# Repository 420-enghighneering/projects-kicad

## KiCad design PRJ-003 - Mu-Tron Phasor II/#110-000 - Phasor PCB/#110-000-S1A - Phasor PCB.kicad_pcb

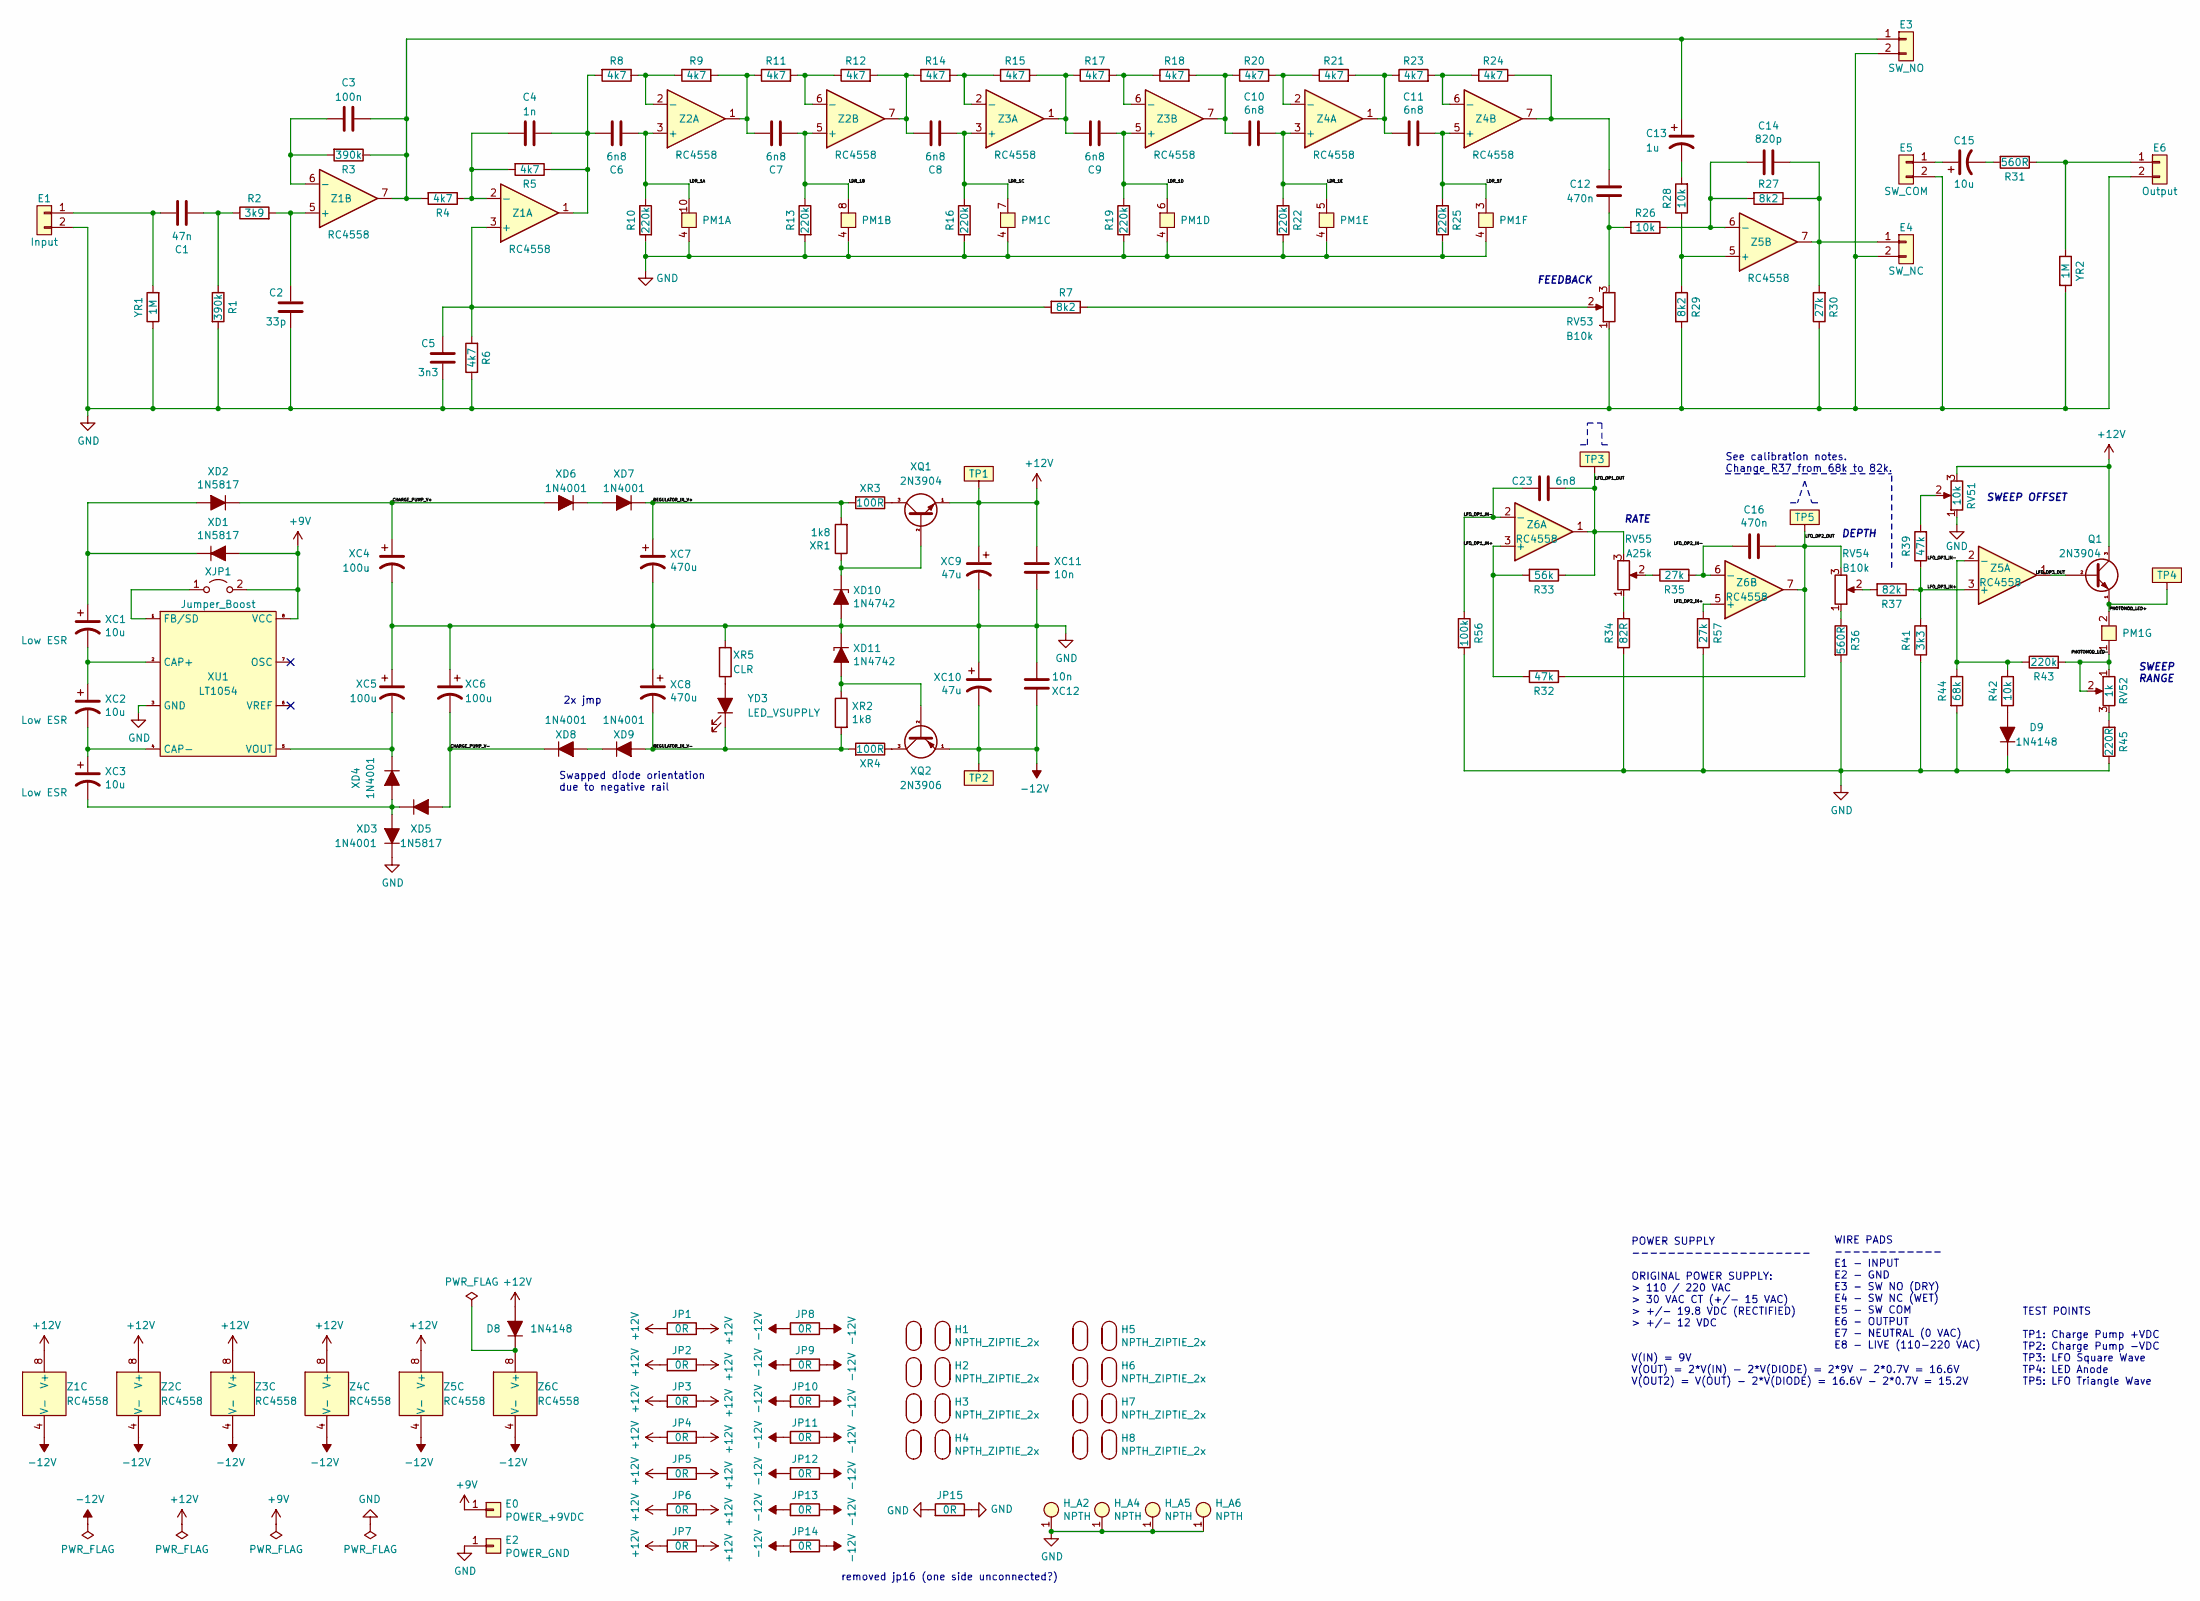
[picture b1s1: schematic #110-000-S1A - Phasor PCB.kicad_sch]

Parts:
C1: 47n; C_MKS2F024701C00KSSD
C2: 33p; C_FKP2O100331D00JSSD
C3: 100n; C_MKS2C031001A00KSSD
C4: 1n; C_FKS2G011001A00KSSD
C5: 3n3; C_FKS2G013301A00KSSD
C6, C7, C8, C9, C10, C11, C23: 6n8; C_FKS2G016801B00KSSD
C12, C16: 470n; C_MKS2C034701C00KSSD
C13: 1u; C_UMA1H010MDD
C14: 820p; C_FKP2J008201D00HSSD
C15: 10u; C_UMA1V100MDD
D8, D9: 1N4148; D_P10.16_DO35
E0: POWER_+9VDC; E_WIRE_PAD_1x_ZIPTIE_NPTH_2x
E1: Input; E_WIRE_PAD_1x_SHIELD_PAD_1x_ZIPTIE_NPTH_2x
E2: POWER_GND; E_WIRE_PAD_1x_ZIPTIE_NPTH_2x
E3: SW_NO; E_WIRE_PAD_1x_SHIELD_PAD_1x_ZIPTIE_NPTH_2x
E4: SW_NC; E_WIRE_PAD_1x_SHIELD_PAD_1x_ZIPTIE_NPTH_2x
E5: SW_COM; E_WIRE_PAD_1x_SHIELD_PAD_1x_ZIPTIE_NPTH_2x
E6: Output; E_WIRE_PAD_1x_SHIELD_PAD_1x_ZIPTIE_NPTH_2x
H1, H2, H3, H4, H5, H6, H7, H8: NPTH_ZIPTIE_2x; E_ZIPTIE_NPTH_2x_P2.54mm
H_A2, H_A4, H_A5, H_A6: NPTH; E_MH_PAD_M3_VIA_HEXSPACER
JP1, JP2, JP3, JP4, JP5, JP6, JP7, JP8, JP9, JP10, JP11, JP12, JP13, JP14, JP15: 0R; R_0R_JUMPER_P10.16
PM1: Photomodule; PM_DIP-10
Q1: 2N3904; Q_P2.54
R1, R3: 390k; R_CF_P10.16_390k
R2: 3k9; R_CF_P10.16_3k9
R4, R5, R6, R8, R9, R11, R12, R14, R15, R17, R18, R20, R21, R23, R24: 4k7; R_CF_P10.16_4k7
R7, R27, R29: 8k2; R_CF_P10.16_8k2
R10, R13, R16, R19, R22, R25, R43: 220k; R_CF_P10.16_220k
R26, R28, R42: 10k; R_CF_P10.16_10k
R30, R35, R57: 27k; R_CF_P10.16_27k
R31, R36: 560R; R_CF_P10.16_560R
R32, R39: 47k; R_CF_P10.16_47k
R33: 56k; R_CF_P10.16_56k
R34: 82R; R_CF_P10.16_82R
R37: 82k; R_CF_P10.16_82k
R41: 3k3; R_CF_P10.16_3k3
R44: 68k; R_CF_P10.16_68k
R45: 220R; R_CF_P10.16_220R
R56: 100k; R_CF_P10.16_100k
RV51: 10k; R_TRIM
RV52: 1k; R_TRIM
RV53, RV54: B10k; R_POT
RV55: A25k; R_POT
TP1: TP1; TP_SMD_R_3mm
TP2: TP2; TP_SMD_R_3mm
TP3: TP3; TP_SMD_R_3mm
TP4, TP5: TP5; TP_SMD_R_3mm
XC1, XC2, XC3: 10u; C_UMA1V100MDD
XC4, XC5, XC6: 100u; C_UMA1E101MDD
XC7, XC8: 470u; C_ANGLED
XC9, XC10: 47u; C_UMA1V470MDD
XC11, XC12: 10n; C_FKS2G021001C00KSSD
XD1, XD2, XD5: 1N5817; D_P10.16_5817
XD3, XD4, XD6, XD7, XD8, XD9: 1N4001; D_P10.16_4001
XD10, XD11: 1N4742; D_P10.16_DO35
XJP1: Jumper_Boost; R_0603_1608M
XQ1: 2N3904; Q_P2.54
XQ2: 2N3906; Q_P2.54
XR1, XR2: 1k8; R_CF_P10.16_1k8
XR3, XR4: 100R; R_CF_P10.16_100R
XR5: CLR; R_CF_P10.16_2k2
XU1: LT1054; U_DIP-8_LT1054_SOCKETED
YD3: LED_VSUPPLY; E_WIRE_PAD_2x_ZIPTIE_NPTH_2x_CIRC
YR1, YR2: 1M; R_CF_P10.16_1M
Z1, Z2, Z3, Z4, Z5, Z6: RC4558; U_DIP-8

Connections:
+9V: E0.1, XD1.1 (A), XJP1.2 (B), XU1.8 (VCC)
+12V: D8.1 (A), JP1.1, JP1.2, JP2.1, JP2.2, JP3.1, JP3.2, JP4.1, JP4.2, JP5.1, JP5.2, JP6.1, JP6.2, JP7.1, JP7.2, Q1.3 (C), RV51.3, TP1.1, XC9.1, XC11.1, XQ1.1 (E), Z1.8 (V+), Z2.8 (V+), Z3.8 (V+), Z4.8 (V+), Z5.8 (V+)
-12V: JP8.1, JP8.2, JP9.1, JP9.2, JP10.1, JP10.2, JP11.1, JP11.2, JP12.1, JP12.2, JP13.1, JP13.2, JP14.1, JP14.2, TP2.1, XC10.2, XC12.1, XQ2.1 (E), Z1.4 (V-), Z2.4 (V-), Z3.4 (V-), Z4.4 (V-), Z5.4 (V-), Z6.4 (V-)
/CHARGE_PUMP_V+: XC4.1, XD2.2 (K), XD6.1 (A)
/CHARGE_PUMP_V-: XC6.2, XD5.1 (A), XD8.2 (K)
/LDR_1A: C6.2, PM1.10, R10.1, Z2.3 (+)
/LDR_1B: C7.2, PM1.8, R13.1, Z2.5 (+)
/LDR_1C: C8.2, PM1.7, R16.1, Z3.3 (+)
/LDR_1D: C9.2, PM1.6, R19.1, Z3.5 (+)
/LDR_1E: C10.1, PM1.5, R22.2, Z4.3 (+)
/LDR_1F: C11.1, PM1.3, R25.2, Z4.5 (+)
/LFO_OP1_IN+: R32.1, R33.2, Z6.3 (+)
/LFO_OP1_IN-: C23.1, R56.1, Z6.2 (-)
/LFO_OP1_OUT: C23.2, R33.1, RV55.3, TP3.1, Z6.1
/LFO_OP2_IN+: R57.1, Z6.5 (+)
/LFO_OP2_IN-: C16.1, R35.2, Z6.6 (-)
/LFO_OP2_OUT: C16.2, R32.2, RV54.3, TP5.1, Z6.7
/LFO_OP3_OUT: Q1.2 (B), Z5.1
/PHOTOMOD_LED+: PM1.2, Q1.1 (E), TP4.1
/PHOTOMOD_LED-: PM1.1, R43.2, RV52.1, RV52.2
/REGULATOR_IN_V+: XC7.1, XD7.2 (K), XR1.2, XR3.2
/REGULATOR_IN_V-: XC8.2, XD9.1 (A), XR2.2, XR4.2, YD3.1 (K)
GND: C2.2, C5.2, D9.2 (K), E1.2, E2.1, E3.2, E4.2, E5.2, E6.2, H_A2.1, H_A4.1, H_A5.1, H_A6.1, JP15.1, JP15.2, PM1.4, PM1.9, R1.2, R6.1, R10.2, R13.2, R16.2, R19.2, R22.1, R25.1, R29.2, R30.1, R34.2, R36.2, R41.1, R44.2, R45.1, R56.2, R57.2, RV51.1, RV53.1, XC4.2, XC5.1, XC6.1, XC7.2, XC8.1, XC9.2, XC10.1, XC11.2, XC12.2, XD3.2 (K), XD10.1 (A), XD11.2 (K), XR5.2, XU1.3 (GND), YR1.1, YR2.2
unnamed: C1.1, R1.1, R2.1
unnamed: C1.2, E1.1, YR1.2
unnamed: C2.1, R2.2, Z1.5 (+)
unnamed: C3.2, R3.2, Z1.6 (-)
unnamed: C4.1, C6.1, R5.1, R8.2, Z1.1
unnamed: C4.2, R4.1, R5.2, Z1.2 (-)
unnamed: C5.1, R6.2, R7.2, Z1.3 (+)
unnamed: C7.1, R9.2, R11.1, Z2.1
unnamed: C8.1, R12.2, R14.1, Z2.7
unnamed: C9.1, R15.2, R17.1, Z3.1
unnamed: C10.2, R18.2, R20.1, Z3.7
unnamed: C11.2, R21.2, R23.1, Z4.1
unnamed: C12.1, R24.1, Z4.7
unnamed: C12.2, R26.2, RV53.3
unnamed: C3.1, C13.1, E3.1, R3.1, R4.2, Z1.7
unnamed: C13.2, R28.2
unnamed: C14.1, R26.1, R27.2, Z5.6 (-)
unnamed: C14.2, E4.1, R27.1, R30.2, Z5.7
unnamed: C15.1, E5.1
unnamed: C15.2, R31.2
unnamed: D8.2 (K), Z6.8 (V+)
unnamed: D9.1 (A), R42.2
unnamed: E6.1, R31.1, YR2.1
unnamed: R7.1, RV53.2
unnamed: R8.1, R9.1, Z2.2 (-)
unnamed: R11.2, R12.1, Z2.6 (-)
unnamed: R14.2, R15.1, Z3.2 (-)
unnamed: R17.2, R18.1, Z3.6 (-)
unnamed: R20.2, R21.1, Z4.2 (-)
unnamed: R23.2, R24.2, Z4.6 (-)
unnamed: R28.1, R29.1, Z5.5 (+)
unnamed: R34.1, RV55.1
unnamed: R35.1, RV55.2
unnamed: R36.1, RV54.1
unnamed: R37.2, RV54.2
unnamed: R39.2, RV51.2
unnamed: R45.2, RV52.3
unnamed: XC1.1, XD1.2 (K), XD2.1 (A)
unnamed: XC1.2, XC2.1, XU1.2 (CAP+)
unnamed: XC2.2, XC3.1, XU1.4 (CAP-)
unnamed: XC3.2, XD3.1 (A), XD4.1 (A), XD5.2 (K)
unnamed: XC5.2, XD4.2 (K), XU1.5 (VOUT)
unnamed: XD6.2 (K), XD7.1 (A)
unnamed: XD8.1 (A), XD9.2 (K)
unnamed: XD10.2 (K), XQ1.2 (B), XR1.1
unnamed: XD11.1 (A), XQ2.2 (B), XR2.1
unnamed: XJP1.1 (A), XU1.1 (FB/SD)
unnamed: XQ1.3 (C), XR3.1
unnamed: XQ2.3 (C), XR4.1
unnamed: XR5.1, YD3.2 (A)

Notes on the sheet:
Swapped diode orientation due to negative rail
2x jmp
removed jp16 (one side unconnected?)
FEEDBACK
RATE
POWER SUPPLY -------------------- ORIGINAL POWER SUPPLY: > 110 / 220 VAC > 30 VAC CT (+/- 15 VAC) > +/- 19.8 VDC (RECTIFIED) > +/- 12 VDC V(IN) = 9V V(OUT) = 2*V(IN) - 2*V(DIODE) = 2*9V - 2*0.7V = 16.6V V(OUT2) = V(OUT) - 2*V(DIODE) = 16.6V - 2*0.7V = 15.2V
See calibration notes. Change R37 from 68k to 82k.
WIRE PADS ------------ E1 - INPUT E2 - GND E3 - SW NO (DRY) E4 - SW NC (WET) E5 - SW COM E6 - OUTPUT E7 - NEUTRAL (0 VAC) E8 - LIVE (110-220 VAC)
DEPTH
SWEEP OFFSET
TEST POINTS TP1: Charge Pump +VDC TP2: Charge Pump -VDC TP3: LFO Square Wave TP4: LED Anode TP5: LFO Triangle Wave
SWEEP RANGE

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
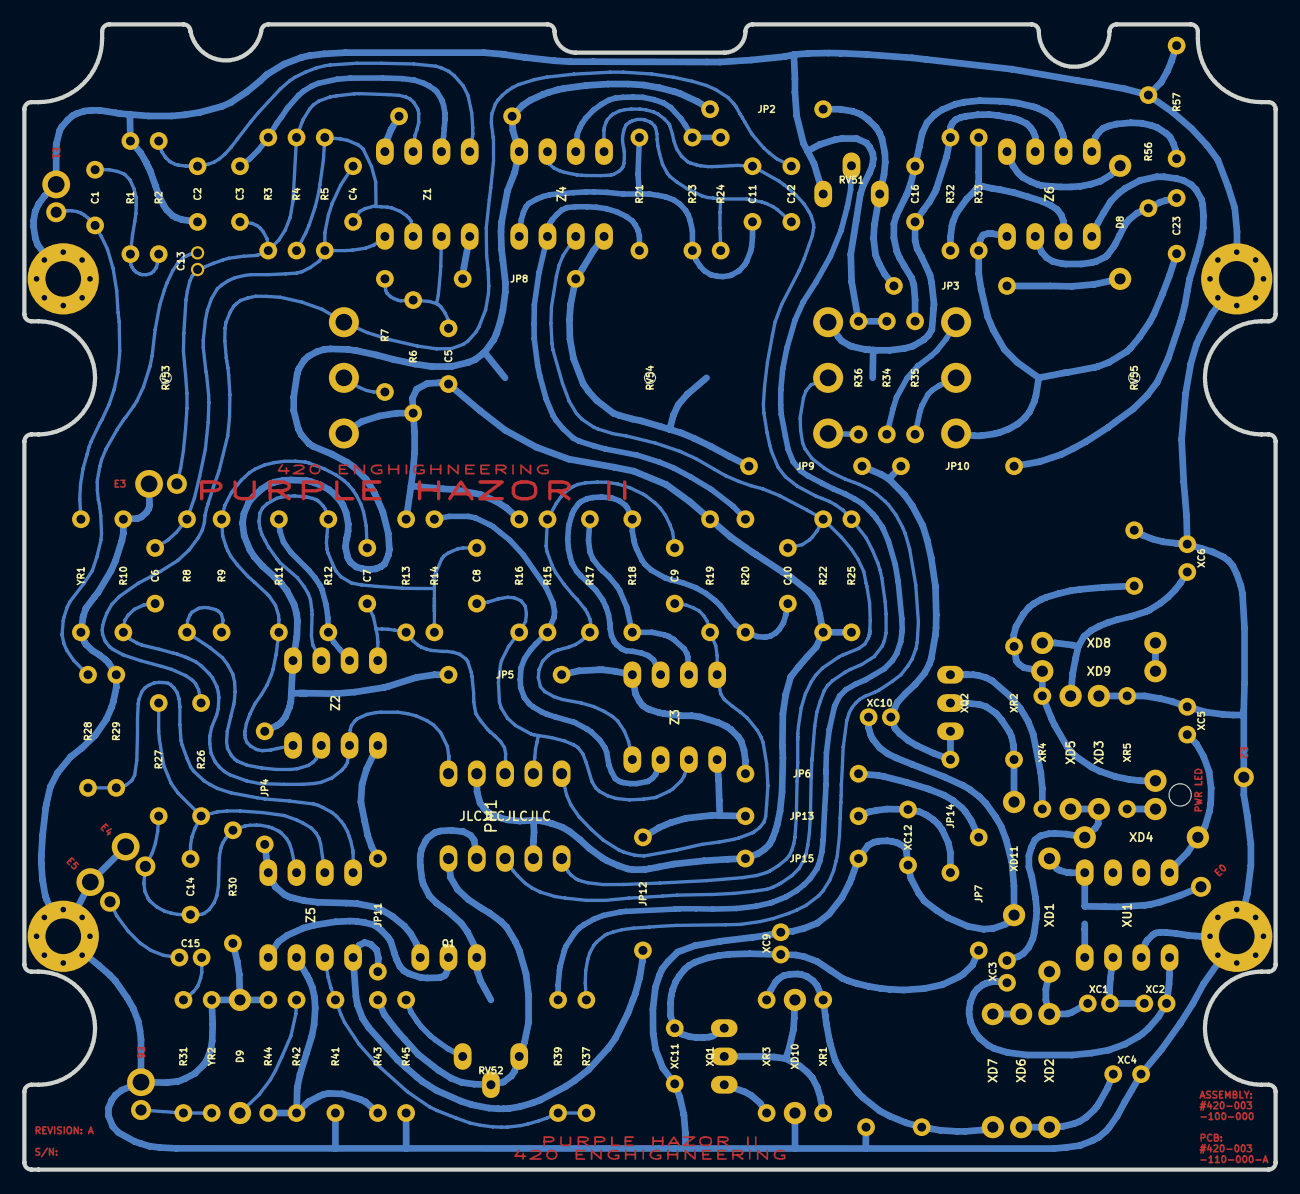
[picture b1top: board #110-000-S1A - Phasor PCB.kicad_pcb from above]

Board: 2 copper layers, 112.4 x 102.9 mm, 151 parts (1 on the bottom side), 75 nets.

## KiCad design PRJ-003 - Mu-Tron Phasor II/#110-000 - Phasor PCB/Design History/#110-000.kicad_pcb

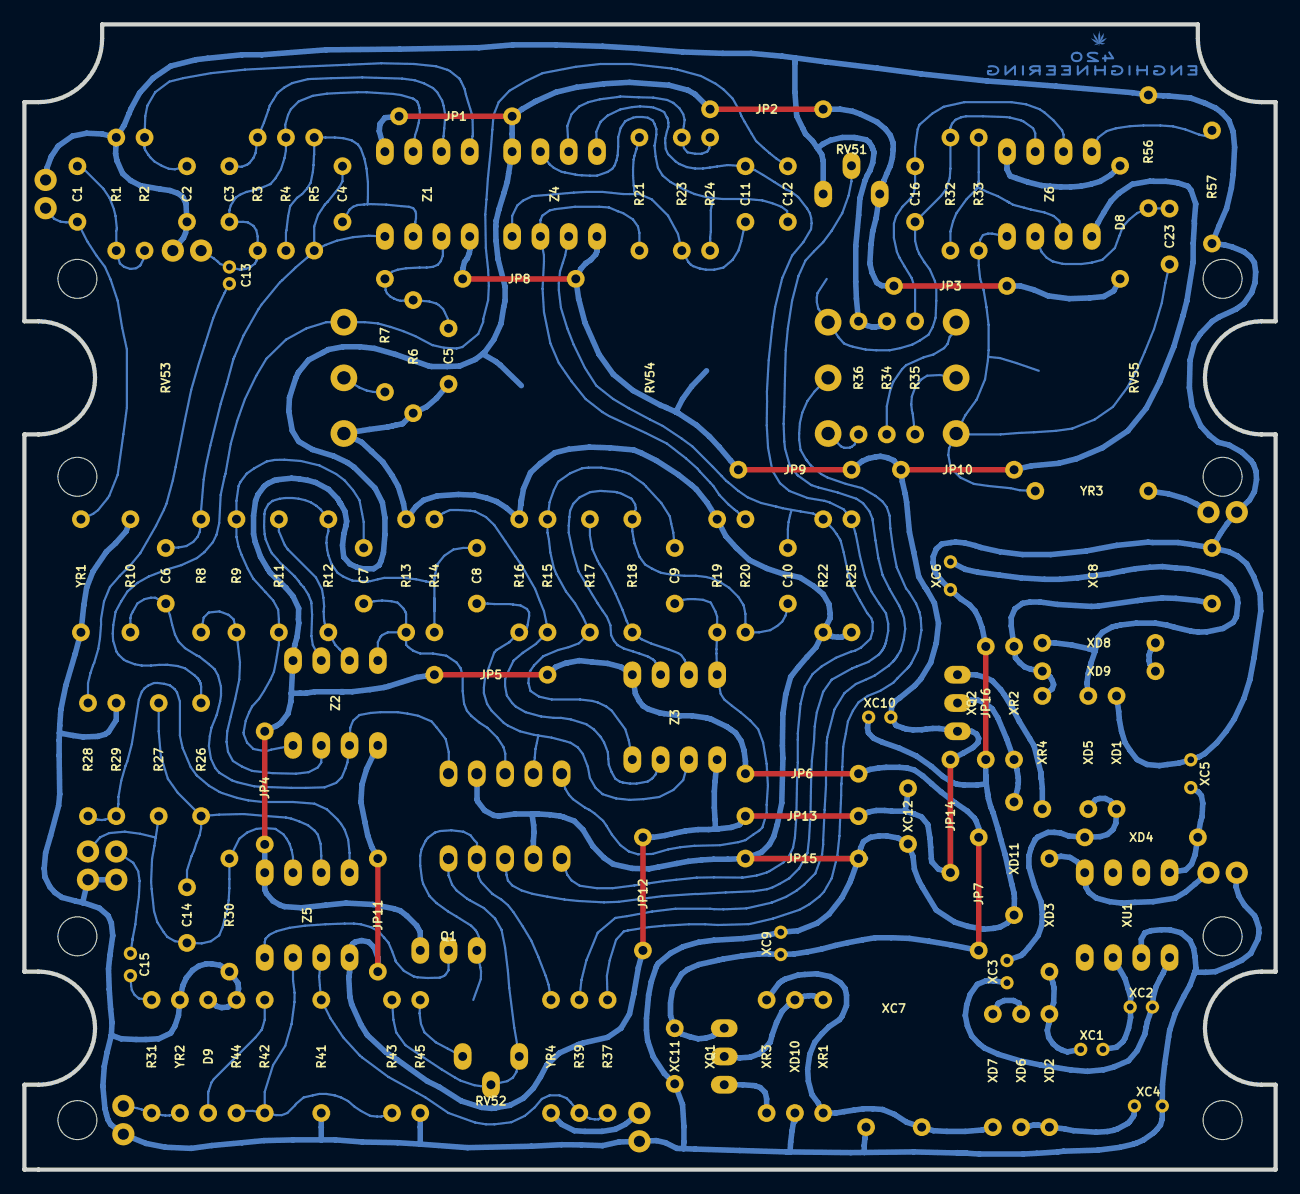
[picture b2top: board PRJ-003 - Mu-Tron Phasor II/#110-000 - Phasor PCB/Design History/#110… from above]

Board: 2 copper layers, 112.4 x 102.9 mm, 155 parts (0 on the bottom side), 75 nets.

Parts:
C1: 47n; C_MKS2F024701C00KSSD
C2: 33p; C_FKP2O100331D00JSSD
C3: 100n; C_MKS2C031001A00KSSD
C4: 1n; C_FKS2G011001A00KSSD
C5: 3n3; C_FKS2G013301A00KSSD
C6, C7, C8, C9, C10, C11, C23: 6n8; C_FKS2G016801B00KSSD
C12, C16: 470n; C_MKS2C034701C00KSSD
C13: 1u; C_UMA1H010MDD
C14: 820p; C_FKP2J008201D00HSSD
C15: 10u; C_UMA1V100MDD
D8, D9: 1N4148; D_P10.16_DO35
E0: Power Supply; E_WIRE_PAD_2x
E1: Input & Shield; E_WIRE_PAD_2x
E3: SW_NO; E_WIRE_PAD_2x
E4: SW_NC; E_WIRE_PAD_2x
E5: SW_COM; E_WIRE_PAD_2x
E6: Output & Shield; E_WIRE_PAD_2x
G1: Logo; Logo_36kdpi
H_A1, H_A2, H_A3, H_A4, H_A5, H_A6, H_A7, H_A8: NPTH; H_NPTH
H_B1, H_B2, H_B3, H_B4, H_B5, H_B6: NPTH; E_ZIPTIE_NPTH
JP1, JP2, JP3, JP4, JP5, JP6, JP7, JP8, JP9, JP10, JP11, JP12, JP13, JP14, JP15, JP16: 0R; R_0R_JUMPER_P10.16
PM1: Photomodule; PM_DIP-10
Q1: 2N3904; Q_P2.54
R1, R3: 390k; R_P10.16
R2: 3k9; R_P10.16
R4, R5, R6, R8, R9, R11, R12, R14, R15, R17, R18, R20, R21, R23, R24: 4k7; R_P10.16
R7, R27, R29: 8k2; R_P10.16
R10, R13, R16, R19, R22, R25, R43: 220k; R_P10.16
R26, R28, R42: 10k; R_P10.16
R30, R35, R57: 27k; R_P10.16
R31, R36: 560R; R_P10.16
R32, R39: 47k; R_P10.16
R33: 56k; R_P10.16
R34: 82R; R_P10.16
R37: 82k; R_P10.16
R41: 3k3; R_P10.16
R44: 68k; R_P10.16
R45: 220R; R_P10.16
R56: 100k; R_P10.16
RV51: 10k; R_TRIM
RV52: 1k; R_TRIM
RV53, RV54: B10k; R_POT
RV55: A25k; R_POT
TP1: TP1; TP_SMD_R_3mm
TP2: TP2; TP_SMD_R_3mm
TP3: TP3; TP_SMD_R_3mm
TP4: TP4; TP_SMD_R_3mm
TP5: TP5; TP_SMD_R_3mm
XC1, XC2, XC3: 10u; C_UMA1V100MDD
XC4, XC5, XC6: 100u; C_UMA1E101MDD
XC7, XC8: 470u; C_ANGLED
XC9, XC10: 47u; C_UMA1V470MDD
XC11, XC12: 10n; C_FKS2G021001C00KSSD
XD1, XD4, XD5, XD6, XD7, XD8, XD9: 1N4001; D_P10.16
XD2, XD3: 1N5817; D_P10.16
XD10, XD11: 1N4742; D_P10.16_DO35
XQ1: 2N3904; Q_P2.54
XQ2: 2N3906; Q_P2.54
XR1, XR2: 1k8; R_P10.16
XR3, XR4: 100R; R_P10.16
XU1: LT1054; U_DIP-8
YD1: LED_RATE_1; E_WIRE_PAD_2x
YD2: LED_RATE_2; E_WIRE_PAD_2x
YR1, YR2: 1M; R_P10.16
YR3, YR4: CLR; R_P10.16
Z1, Z2, Z3, Z4, Z5, Z6: 4558; U_DIP-8

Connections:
+9V: E0.1, XD3.1, XU1.8
+12V: D8.1, JP1.1, JP1.2, JP2.1, JP2.2, JP3.1, JP3.2, JP4.1, JP4.2, JP5.1, JP5.2, JP6.1, JP6.2, JP7.1, JP7.2, Q1.3, RV51.3, TP1.1, XC9.1, XC11.1, XQ1.1, Z1.8, Z2.8, Z3.8, Z4.8, Z5.8
-12V: JP8.1, JP8.2, JP9.1, JP9.2, JP10.1, JP10.2, JP11.1, JP11.2, JP12.1, JP12.2, JP13.1, JP13.2, JP14.1, JP14.2, TP2.1, XC10.2, XC12.2, XQ2.1, Z1.4, Z2.4, Z3.4, Z4.4, Z5.4, Z6.4
GND: C2.2, C5.2, D9.2, E0.2, E1.2, E3.2, E4.2, E5.2, E6.2, JP15.1, JP15.2, JP16.1, JP16.2, PM1.4, PM1.9, R1.1, R6.2, R10.2, R13.2, R16.2, R19.2, R22.2, R25.2, R29.1, R30.1, R34.1, R36.1, R41.2, R44.1, R45.2, R56.1, R57.1, RV51.1, RV53.1, XC4.2, XC5.1, XC6.1, XC7.2, XC8.1, XC9.2, XC10.1, XC11.2, XC12.1, XD1.2, XD10.1, XD11.2, XU1.3, YD1.1, YD2.1, YR1.1, YR2.1
unnamed: C1.1, E1.1, YR1.2
unnamed: C1.2, R1.2, R2.1
unnamed: C2.1, R2.2, Z1.5
unnamed: C3.1, R3.1, Z1.6
unnamed: C4.1, R4.2, R5.1, Z1.2
unnamed: C4.2, C6.1, R5.2, R8.2, Z1.1
unnamed: C5.1, R6.1, R7.2, Z1.3
unnamed: C6.2, PM1.10, R10.1, Z2.3
unnamed: C7.1, R9.1, R11.2, Z2.1
unnamed: C7.2, PM1.8, R13.1, Z2.5
unnamed: C8.1, R12.1, R14.2, Z2.7
unnamed: C8.2, PM1.7, R16.1, Z3.3
unnamed: C9.1, R15.1, R17.2, Z3.1
unnamed: C9.2, PM1.6, R19.1, Z3.5
unnamed: C10.1, R18.1, R20.2, Z3.7
unnamed: C10.2, PM1.5, R22.1, Z4.3
unnamed: C11.1, R21.1, R23.2, Z4.1
unnamed: C11.2, PM1.3, R25.1, Z4.5
unnamed: C12.1, R24.1, Z4.7
unnamed: C12.2, R26.2, RV53.3
unnamed: C3.2, C13.1, E3.1, R3.2, R4.1, Z1.7
unnamed: C13.2, R28.2
unnamed: C14.1, R26.1, R27.2, Z5.6
unnamed: C14.2, E4.1, R27.1, R30.2, Z5.7
unnamed: C15.1, E5.1
unnamed: C15.2, R31.1
unnamed: C16.1, R35.1, Z6.6
unnamed: C16.2, R32.1, RV54.3, TP5.1, Z6.7
unnamed: C23.1, R56.2, Z6.2
unnamed: C23.2, R33.1, RV55.3, TP3.1, YR3.2, Z6.1
unnamed: D8.2, Z6.8
unnamed: D9.1, R42.1
unnamed: E6.1, R31.2, YR2.2
unnamed: PM1.1, R43.1, RV52.1, RV52.2
unnamed: PM1.2, Q1.1, TP4.1, YR4.2
unnamed: Q1.2, Z5.1
unnamed: R7.1, RV53.2
unnamed: R8.1, R9.2, Z2.2
unnamed: R11.1, R12.2, Z2.6
unnamed: R14.1, R15.2, Z3.2
unnamed: R17.1, R18.2, Z3.6
unnamed: R20.1, R21.2, Z4.2
unnamed: R23.1, R24.2, Z4.6
unnamed: R28.1, R29.2, Z5.5
unnamed: R32.2, R33.2, Z6.3
unnamed: R34.2, RV55.1
unnamed: R35.2, RV55.2
unnamed: R36.2, RV54.1
unnamed: R37.1, RV54.2
unnamed: R37.2, R39.2, R41.1, Z5.3
unnamed: R39.1, RV51.2
unnamed: R42.2, R43.2, R44.2, Z5.2
unnamed: R45.1, RV52.3
unnamed: R57.2, Z6.5
unnamed: XC1.1, XD2.1, XD3.2
unnamed: XC1.2, XC2.1, XU1.2
unnamed: XC2.2, XC3.1, XU1.4
unnamed: XC3.2, XD1.1, XD4.1, XD5.2
unnamed: XC4.1, XD2.2, XD6.1
unnamed: XC5.2, XD4.2, XU1.5
unnamed: XC6.2, XD5.1, XD8.1
unnamed: XC7.1, XD7.2, XR1.1, XR3.2
unnamed: XC8.2, XD9.2, XR2.2, XR4.2
unnamed: XD6.2, XD7.1
unnamed: XD8.2, XD9.1
unnamed: XD10.2, XQ1.2, XR1.2
unnamed: XD11.1, XQ2.2, XR2.1
unnamed: XQ1.3, XR3.1
unnamed: XQ2.3, XR4.1
unnamed: YD1.2, YR3.1
unnamed: YD2.2, YR4.1

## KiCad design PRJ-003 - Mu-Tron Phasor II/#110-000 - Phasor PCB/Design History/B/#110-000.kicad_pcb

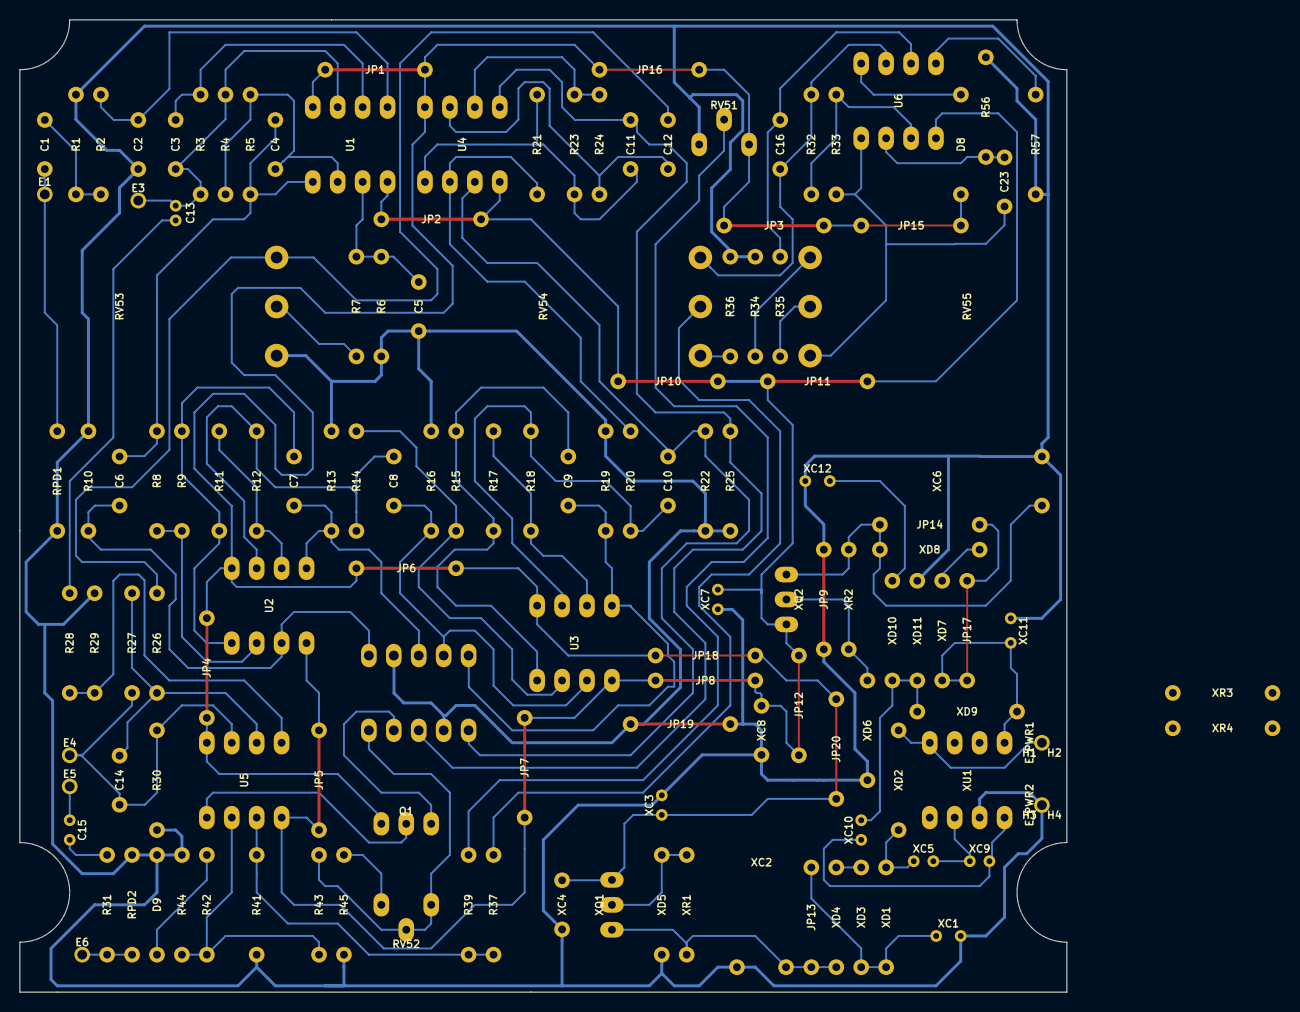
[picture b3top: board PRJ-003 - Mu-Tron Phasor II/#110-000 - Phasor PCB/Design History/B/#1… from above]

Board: 2 copper layers, 106.7 x 99.1 mm, 142 parts (0 on the bottom side), 73 nets.

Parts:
C1: 47n; C_MKS2F024701C00KSSD
C2: 33p; C_FKP2O100331D00JSSD
C3: 100n; C_MKS2C031001A00KSSD
C4: 1n; C_FKS2G011001A00KSSD
C5: 3n3; C_FKS2G013301A00KSSD
C6, C7, C8, C9, C10, C11, C23: 6n8; C_FKS2G016801B00KSSD
C12, C16: 470n; C_MKS2C034701C00KSSD
C13: 1u; C_UMA1H010MDD
C14: 820p; C_FKP2J008201D00HSSD
C15: 10u; C_UMA1V100MDD
D8, D9: 1N4148; D_P10.16
E1: Input; E_WIRE_PAD
E3: SW_NO; E_WIRE_PAD
E4: SW_NC; E_WIRE_PAD
E5: SW_COM; E_WIRE_PAD
E6: Output; E_WIRE_PAD
E_PWR1: +9VDC; E_WIRE_PAD
E_PWR2: GND; E_WIRE_PAD
H1, H2, H3, H4, H5, H6: NPTH; E_ZIPTIE_NPTH
JP1, JP2, JP3, JP4, JP5, JP6, JP7, JP8, JP9, JP10, JP11, JP12, JP15, JP16, JP17, JP18, JP19, JP20: 0R; R_0R_JUMPER_P10.16
JP13, JP14: Jumper_NO; R_NO_JUMPER_P10.16
PM1: Photomodule; PM_DIP-10
Q1: 2N3904; Q_P2.54
R1, R3: 390k; R_P10.16
R2: 3k9; R_P10.16
R4, R5, R6, R8, R9, R11, R12, R14, R15, R17, R18, R20, R21, R23, R24: 4k7; R_P10.16
R7, R27, R29: 8k2; R_P10.16
R10, R13, R16, R19, R22, R25, R43: 220k; R_P10.16
R26, R28, R42: 10k; R_P10.16
R30, R35, R57: 27k; R_P10.16
R31, R36: 560R; R_P10.16
R32, R39: 47k; R_P10.16
R33: 56k; R_P10.16
R34: 82R; R_P10.16
R37: 82k; R_P10.16
R41: 3k3; R_P10.16
R44: 68k; R_P10.16
R45: 220R; R_P10.16
R56: 100k; R_P10.16
RPD1, RPD2: 1M; R_P10.16
RV51: 10k; R_TRIM
RV52: 1k; R_TRIM
RV53, RV54: B10k; R_POT
RV55: A25k; R_POT
U1, U2, U3, U4, U5, U6: 4558; U_DIP-8
XC1, XC11, XC12: 100u; C_UMA1E101MDD
XC2, XC6: 470u; C_ANGLED
XC3, XC7: 47u; C_UMA1V470MDD
XC4, XC8: 10n; C_FKS2G021001C00KSSD
XC5, XC9, XC10: 10u; C_UMA1V100MDD
XD1, XD2: 1N5817; D_P10.16
XD3, XD4, XD7, XD8, XD9, XD10, XD11: 1N4001; D_P10.16
XD5, XD6: 1N4742; D_P10.16
XQ1: 2N3904; Q_P2.54
XQ2: 2N3906; Q_P2.54
XR1, XR2: 1k8; R_P10.16
XR3, XR4: 100R; R_P10.16
XU1: LT1054; U_DIP-8

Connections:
+9V: E_PWR1.1, XD2.1, XU1.8
+12V: D8.1, JP1.1, JP1.2, JP3.1, JP3.2, JP4.1, JP4.2, JP6.1, JP6.2, JP15.1, JP15.2, JP16.1, JP16.2, JP18.1, JP18.2, JP20.1, JP20.2, Q1.3, RV51.3, U1.8, U2.8, U3.8, U4.8, U5.8, XC3.1, XC4.1, XQ1.1
-12V: JP2.1, JP2.2, JP5.1, JP5.2, JP7.1, JP7.2, JP8.1, JP8.2, JP10.1, JP10.2, JP11.1, JP11.2, JP12.1, JP12.2, U1.4, U2.4, U3.4, U4.4, U5.4, U6.4, XC7.2, XC8.2, XQ2.1
/jmp: JP14.1, JP17.1, JP17.2, XC11.2, XD7.1, XD9.2, XU1.5
GND: C2.2, C5.2, D9.2, E_PWR2.1, JP9.1, JP9.2, JP19.1, JP19.2, PM1.4, PM1.9, R1.1, R6.2, R10.2, R13.2, R16.2, R19.2, R22.2, R25.2, R29.1, R30.1, R34.1, R36.1, R41.2, R44.1, R45.2, R56.1, R57.1, RPD1.1, RPD2.1, RV51.1, RV53.1, XC1.2, XC2.2, XC3.2, XC4.2, XC6.1, XC7.1, XC8.1, XC11.1, XC12.1, XD5.1, XD6.2, XD11.2, XU1.3
unnamed: C1.1, E1.1, RPD1.2
unnamed: C1.2, R1.2, R2.1
unnamed: C2.1, R2.2, U1.5
unnamed: C3.1, R3.1, U1.6
unnamed: C4.1, R4.2, R5.1, U1.2
unnamed: C4.2, C6.1, R5.2, R8.2, U1.1
unnamed: C5.1, R6.1, R7.2, U1.3
unnamed: C6.2, PM1.10, R10.1, U2.3
unnamed: C7.1, R9.1, R11.2, U2.1
unnamed: C7.2, PM1.8, R13.1, U2.5
unnamed: C8.1, R12.1, R14.2, U2.7
unnamed: C8.2, PM1.7, R16.1, U3.3
unnamed: C9.1, R15.1, R17.2, U3.1
unnamed: C9.2, PM1.6, R19.1, U3.5
unnamed: C10.1, R18.1, R20.2, U3.7
unnamed: C10.2, PM1.5, R22.1, U4.3
unnamed: C11.1, R21.1, R23.2, U4.1
unnamed: C11.2, PM1.3, R25.1, U4.5
unnamed: C12.1, R24.1, U4.7
unnamed: C12.2, R26.2, RV53.3
unnamed: C3.2, C13.1, E3.1, R3.2, R4.1, U1.7
unnamed: C13.2, R28.2
unnamed: C14.1, R26.1, R27.2, U5.6
unnamed: C14.2, E4.1, R27.1, R30.2, U5.7
unnamed: C15.1, E5.1
unnamed: C15.2, R31.1
unnamed: C16.1, R35.1, U6.6
unnamed: C16.2, R32.1, RV54.3, U6.7
unnamed: C23.1, R56.2, U6.2
unnamed: C23.2, R33.1, RV55.3, U6.1
unnamed: D8.2, U6.8
unnamed: D9.1, R42.1
unnamed: E6.1, R31.2, RPD2.2
unnamed: JP13.1, XC1.1, XD1.2, XD3.1
unnamed: JP13.2, XC2.1, XD4.2, XR1.1, XR3.2
unnamed: JP14.2, XC6.2, XD8.2, XR2.2, XR4.2
unnamed: PM1.1, R43.1, RV52.1, RV52.2
unnamed: PM1.2, Q1.1
unnamed: Q1.2, U5.1
unnamed: R7.1, RV53.2
unnamed: R8.1, R9.2, U2.2
unnamed: R11.1, R12.2, U2.6
unnamed: R14.1, R15.2, U3.2
unnamed: R17.1, R18.2, U3.6
unnamed: R20.1, R21.2, U4.2
unnamed: R23.1, R24.2, U4.6
unnamed: R28.1, R29.2, U5.5
unnamed: R32.2, R33.2, U6.3
unnamed: R34.2, RV55.1
unnamed: R35.2, RV55.2
unnamed: R36.2, RV54.1
unnamed: R37.1, RV54.2
unnamed: R37.2, R39.2, R41.1, U5.3
unnamed: R39.1, RV51.2
unnamed: R42.2, R43.2, R44.2, U5.2
unnamed: R45.1, RV52.3
unnamed: R57.2, U6.5
unnamed: XC5.1, XD1.1, XD2.2
unnamed: XC5.2, XC9.1, XU1.2
unnamed: XC9.2, XC10.1, XU1.4
unnamed: XC10.2, XD9.1, XD10.2, XD11.1
unnamed: XC12.2, XD10.1
unnamed: XD3.2, XD4.1
unnamed: XD5.2, XQ1.2, XR1.2
unnamed: XD6.1, XQ2.2, XR2.1
unnamed: XD7.2, XD8.1
unnamed: XQ1.3, XR3.1
unnamed: XQ2.3, XR4.1
